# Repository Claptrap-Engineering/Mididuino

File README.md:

# Midi-duino
A midicontroller based on an arduino nano

The original code can be downloaded from https://drive.google.com/file/d/0BwnVMB_6yujwR1dydVJ6MHJib2M/view
This code is written by Dave from notes and volts @ https://www.notesandvolts.com 
Watch his youtube movies to make your own version of a midi controller.

After toying around on a breadboard and converting this to a solder strip board.
I got annoyed by the prototyping process and started designing a PCB for it.
This project is the result :)

The arduino you click or solder on this board uses the script you can find on this page in the MIDI_controller folder.
It is a configured version of daves original code to fit two multiplexers that read 16 potentiometers.

To make the code work (compile) in the arduino IDE you must install the midi library files.
You can find these at https://github.com/FortySevenEffects/arduino_midi_library/releases/tag/4.2

Notes for soldering:

Solder the parts in the order from small to large.
Solder the two pinheader sockets in the top holes at the back of the board, leaving the two holes open at the bottom,
(when looking at the board in such a way so the printed R potmeter values are in normal reading order)
So that the arduino can be clicked into the sockets at the back of the board. See the images folder for reference pictures.

Din plug pinout (see pinout image in pcb image folder)

Connect pin 1 of the jumpers with pin 5 of the din plug (signal).
Connect pin 2 of the jumpers with pin 2 of the din plug (ground).
Connect pin 3 of the jumpers with pin 4 of the din plug (5v).

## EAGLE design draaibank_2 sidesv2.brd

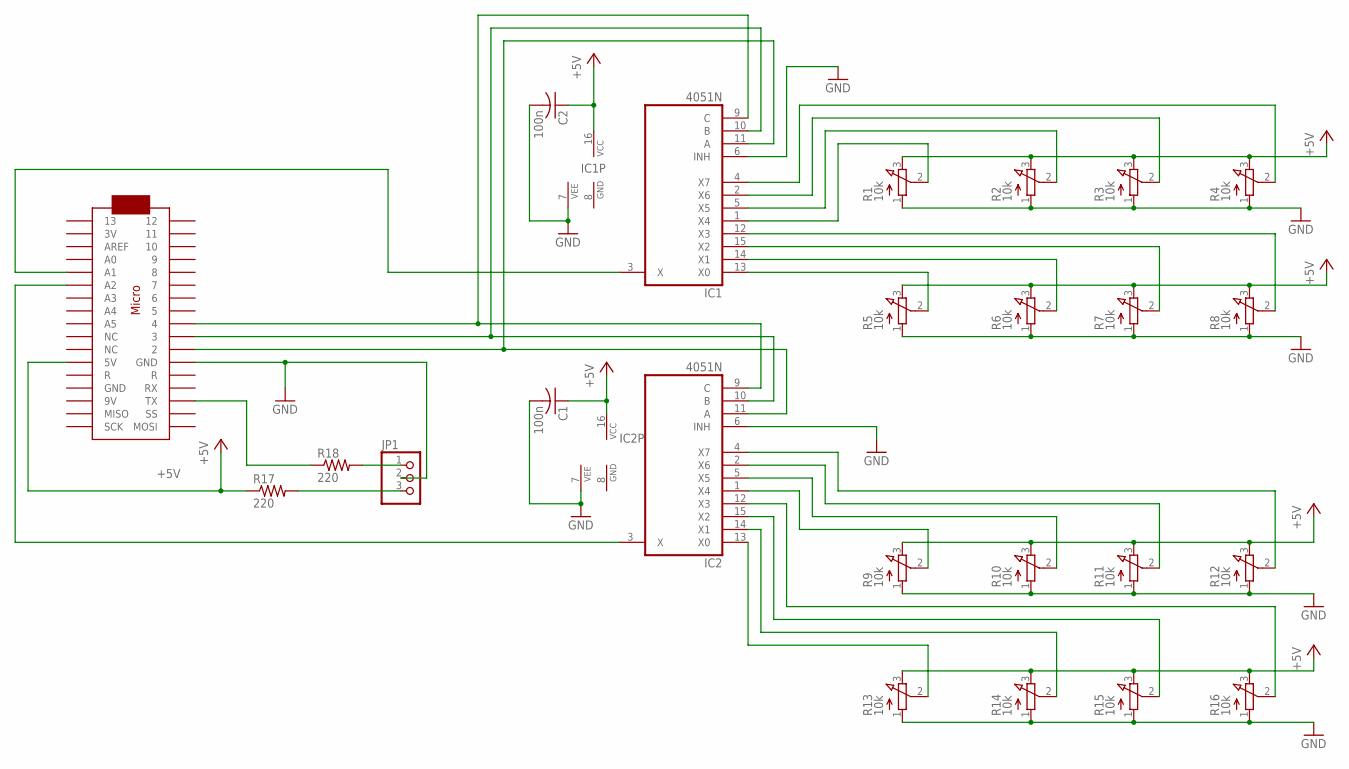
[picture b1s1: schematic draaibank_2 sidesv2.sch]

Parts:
C1, C2: 100n; C0805
IC1, IC2: 4051N; DIL16
JP1: PINHD-1X3; 1X03
R1, R2, R3, R4, R5, R6, R7, R8, R9, R10, R11, R12, R13, R14, R15, R16: 10k; EVUF
R17, R18: 220; R0603
U$1: ARDUINOMICRO

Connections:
+5V: C1.1, C2.1, IC1.16 (VCC), IC2.16 (VCC), R1.3 (E), R2.3 (E), R3.3 (E), R4.3 (E), R5.3 (E), R6.3 (E), R7.3 (E), R8.3 (E), R9.3 (E), R10.3 (E), R11.3 (E), R12.3 (E), R13.3 (E), R14.3 (E), R15.3 (E), R16.3 (E), R17.1, U$1.P$23 (5V)
GND: C1.2, C2.2, IC1.6 (INH), IC1.7 (VEE), IC1.8 (GND), IC2.6 (INH), IC2.7 (VEE), IC2.8 (GND), JP1.2, R1.1 (A), R2.1 (A), R3.1 (A), R4.1 (A), R5.1 (A), R6.1 (A), R7.1 (A), R8.1 (A), R9.1 (A), R10.1 (A), R11.1 (A), R12.1 (A), R13.1 (A), R14.1 (A), R15.1 (A), R16.1 (A), U$1.P$21 (GND)
unnamed: IC2.13 (X0), R13.2 (S)
unnamed: IC2.14 (X1), R14.2 (S)
unnamed: IC2.15 (X2), R15.2 (S)
unnamed: IC2.12 (X3), R16.2 (S)
unnamed: IC2.1 (X4), R9.2 (S)
unnamed: IC2.5 (X5), R10.2 (S)
unnamed: IC2.2 (X6), R11.2 (S)
unnamed: IC2.4 (X7), R12.2 (S)
unnamed: IC1.13 (X0), R5.2 (S)
unnamed: IC1.14 (X1), R6.2 (S)
unnamed: IC1.15 (X2), R7.2 (S)
unnamed: IC1.12 (X3), R8.2 (S)
unnamed: IC1.1 (X4), R1.2 (S)
unnamed: IC1.5 (X5), R2.2 (S)
unnamed: IC1.2 (X6), R3.2 (S)
unnamed: IC1.4 (X7), R4.2 (S)
unnamed: IC1.11 (A), IC2.11 (A), U$1.P$11 (2)
unnamed: IC1.10 (B), IC2.10 (B), U$1.P$10 (3)
unnamed: IC1.9 (C), IC2.9 (C), U$1.P$9 (4)
unnamed: R18.1, U$1.P$15 (TX)
unnamed: JP1.1, R18.2
unnamed: JP1.3, R17.2
unnamed: IC1.3 (X), U$1.P$30 (A1)
unnamed: IC2.3 (X), U$1.P$29 (A2)

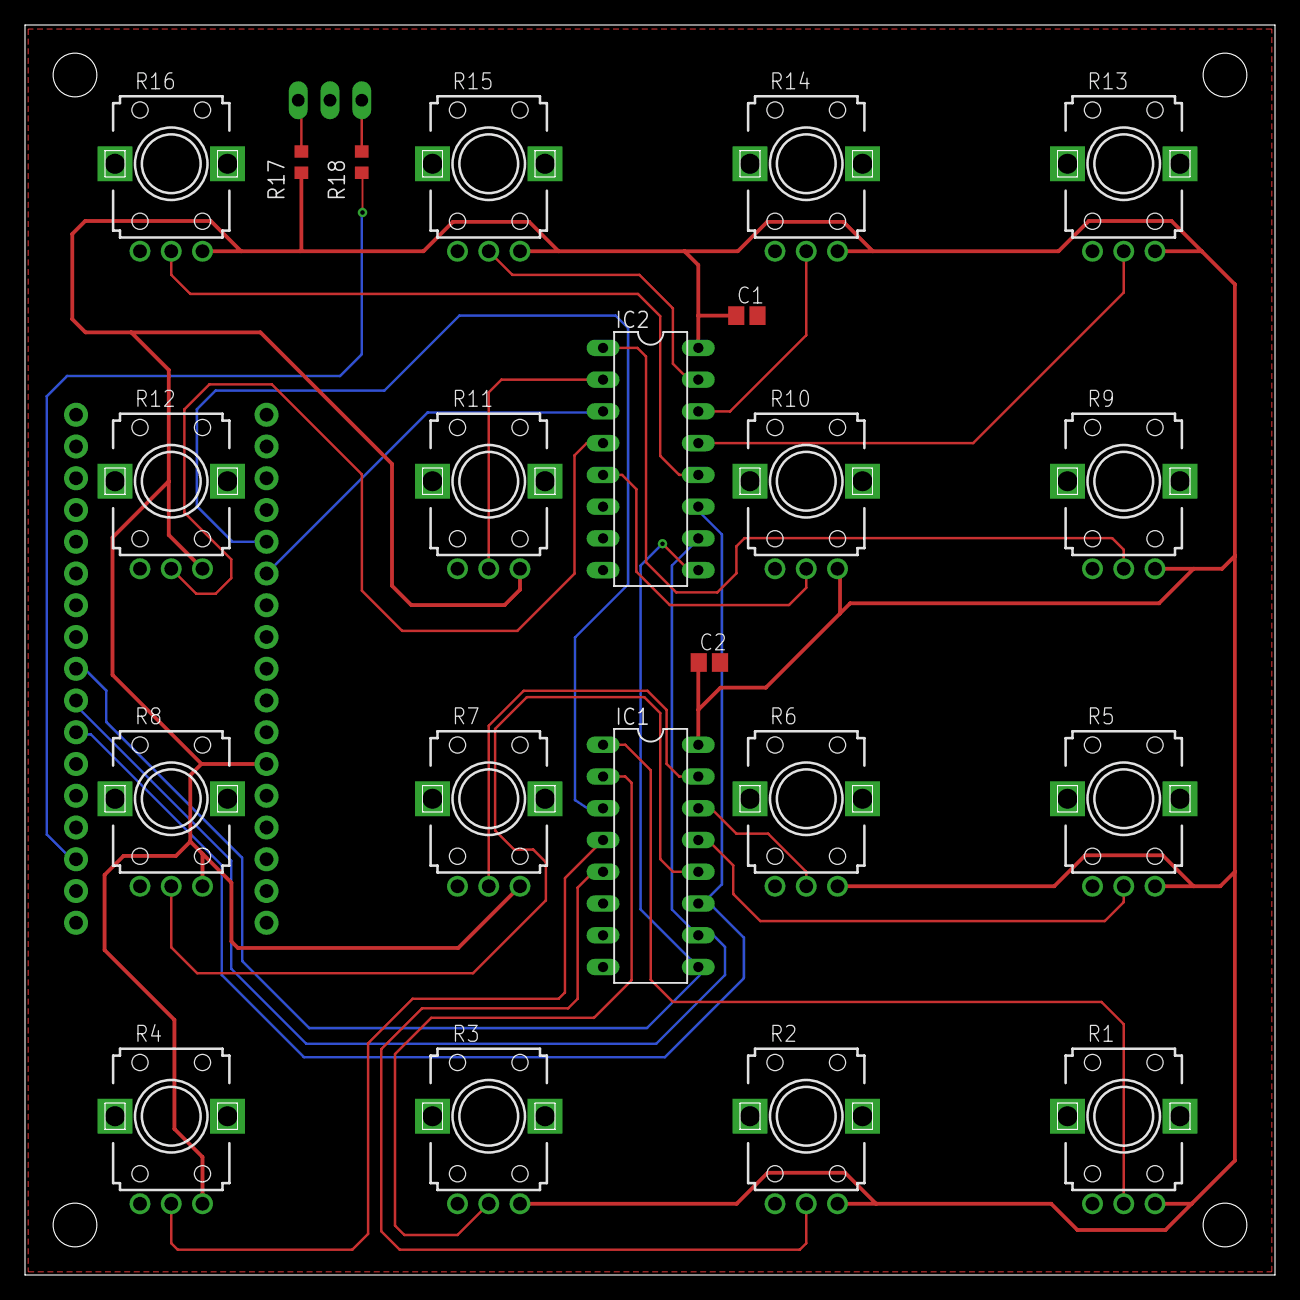
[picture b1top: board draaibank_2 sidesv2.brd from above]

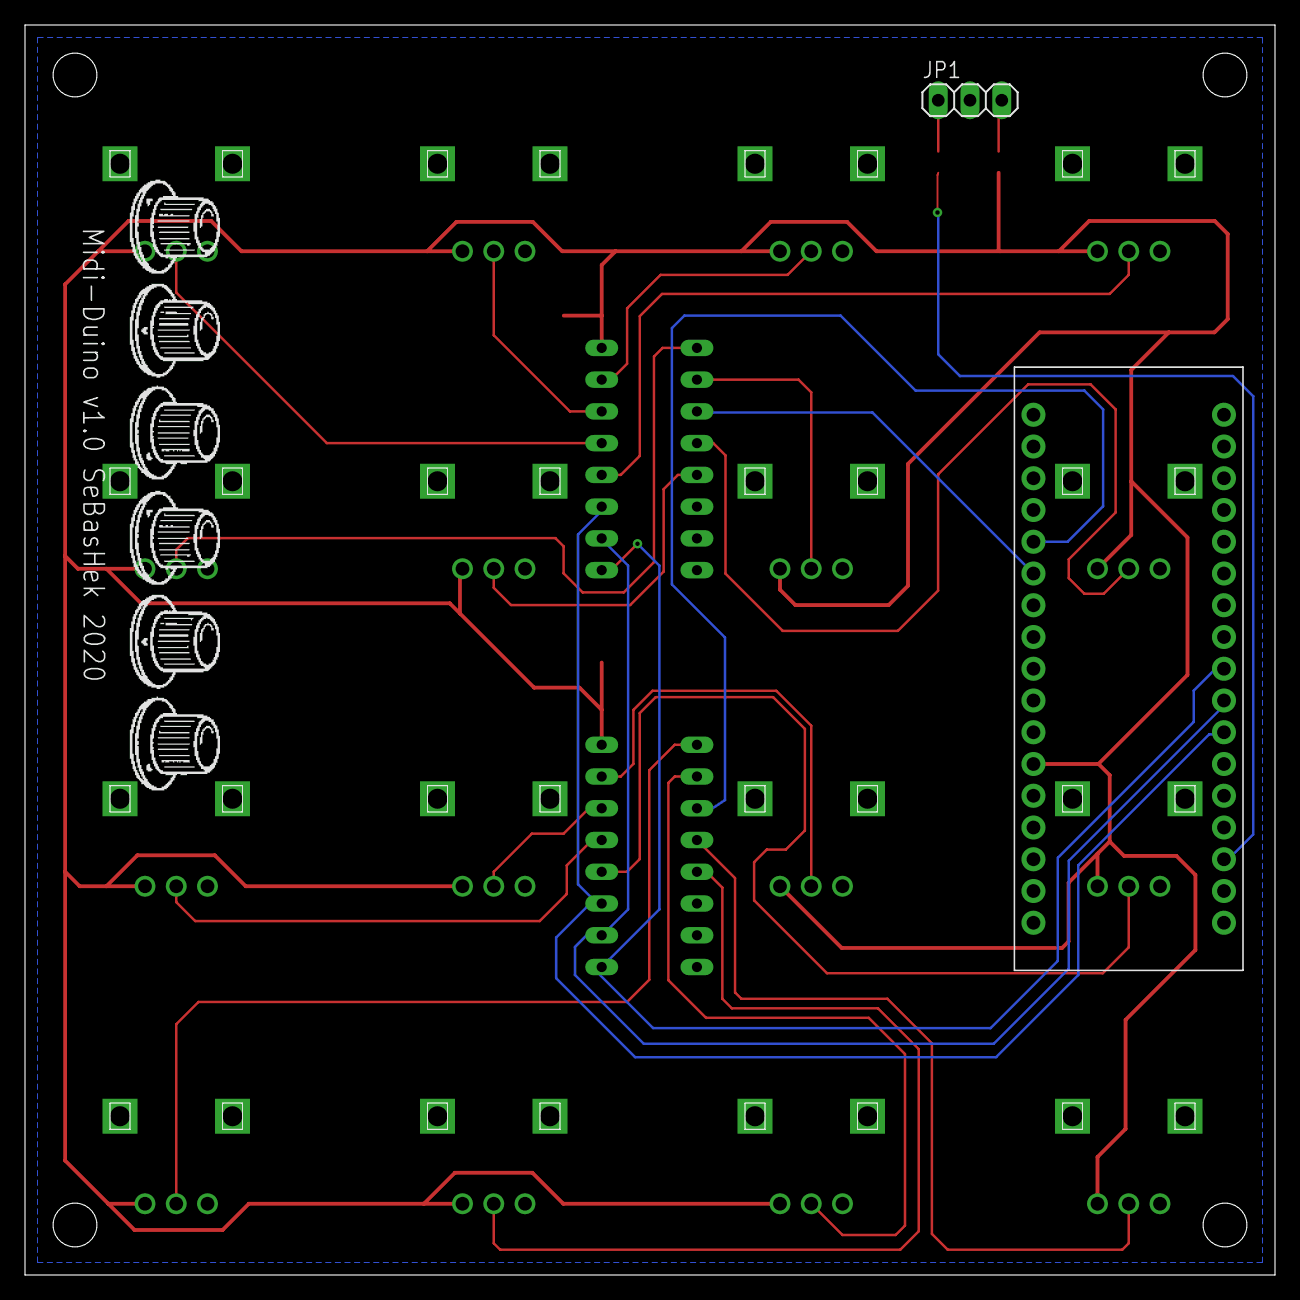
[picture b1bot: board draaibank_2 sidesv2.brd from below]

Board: 2 copper layers, 100.0 x 100.0 mm, 24 parts (2 on the bottom side), 26 nets.

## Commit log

2020-09-29 Add files via upload
    Adapted arduino script to make use of 16 potmeters
2020-09-30 Update MIDI_Controller_v1-2.ino
    changed mux ports to A1 and A2 as routed on mididuino board v1
